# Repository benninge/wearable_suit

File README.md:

# Smart dancing suit

The smart dancing suit project was part of the [Wearable Computing Systems Lab Course](https://es.informatik.uni-freiburg.de/teaching/wearable-lab) during the summer semester of 2017. The idea is to develop an LED covered dancing suit which generates a light show according to the current music and movements of the wearer, instead of running a predefined choreography like it is done in other approaches. This is what makes the suit a “smart" dancing suit.

Therefore the suit is equipped with a couple of sensors, which enable sensing of motions and sound. For the sound measurement, a microphone module is used. The measurement samples are then used to calculate the sound level or to apply a Fourier transform. The music spectrum can be shown on the chest display.
The motion measurements are performed by inertial measurement units (IMUs) which are mounted on hands and feet. This allows movement detection of individual body parts.

## Contents

* [System architecture](https://github.com/benninge/wearable_suit/blob/master/README.md#hardware-architecture)
    * [Mainboard](https://github.com/benninge/wearable_suit/blob/master/README.md#mainboard)
    * [Sensor Board](https://github.com/benninge/wearable_suit/blob/master/README.md#sensor-board)
* [Software](https://github.com/benninge/wearable_suit/blob/master/README.md#software)
    * [Mainboard firmware](https://github.com/benninge/wearable_suit/blob/master/README.md#mainboard-firmware)
    * [Sensor board firmware](https://github.com/benninge/wearable_suit/blob/master/README.md#sensor-board-firmware)
    * [App](https://github.com/benninge/wearable_suit/blob/master/README.md#app)

## Hardware architecture

The system is built according to the hardware architecture given in figure 1. The centerpiece of the system is the mainboard. It contains an STM32 microcontroller, which controls all the other modules. It is connected to the IMU sensor modules over a bus systems and it directly controls all LEDs as well as the microphone module, which is used for music detection. A bluetooth connection to an Android app was also planned, but is currently not implemented.

<figure role="group">
<div align="center"></div> 
<div align="center"><figcaption> Figure 1: Schematic setup of the system </figcaption></div> 
</figure>

### Mainboard

The mainboard consists of an STM32F411E discovery board with a breadboard shield. The shield powers the discovery board and connects it to the sensor boards, the WS2812 RGB LED strips on arms and legs, the 10 x 10 LED display on the chest and the Adafruit MAX9814 microphone module. A wiring diagram of the mainboard shield is shown in figure 2.

<figure role="group">
<div align="center"></div> 
<div align="center"><figcaption> Figure 2: Wiring diagram of the mainboard shield </figcaption></div> 
</figure>

The sensor boards are connected over an RS-485 based bus system. The RS-485 transceiver should be a model with a 3.3V logic level. The chest display and the LED strips have to be connected according to the defines in the header files WS2812.h, ledSuit.h and the source file ledSuit.c of the mainboard firmware (which may be configured according to the used led-strip lengths). Since the LED strips are powered with 5V, each LED strip uses a switching regulator to generate its supply voltage out of the 3s LiPo power supply (which is called VCC here).

### Sensor board

The sensor module is an Arduino compatible custom circuit board. Figure 3 shows an assembled sensor board. The EAGLE files can be found in the "SensorBoard" folder in this repository. The sensor board hardware uses an ATmega328P microcontroller and a MPU-9250 IMU. It is directly powered by the 3s LiPo power supply and connected to the mainboard over the RS-485 bus.

<figure role="group">
<div align="center"></div> 
<div align="center"><figcaption> Figure 3: Sensor board </figcaption></div> 
</figure>

## Software

This project provides a software development kit for the mainboard containing examples. Additionally, a sensor board firmware is provided as well as an incomplete Android app to control the suit with a smartphone.

### Mainboard firmware

The mainboard firmware can be found in the "mainboard" folder. It contains all libraries for developing your own project as well as some example programs which show the capabilities of the provided libraries.

#### Libraries

The module structure of the mainboard firmware is shown in figure 4. The used hardware modules are colored in blue and the libraries are colored in green. The whole suit functionality can easily be accessed through high level functions, provided by the software development kit libraries. The example program libraries show how the software development kit can be used, to program specific applications.

<figure role="group">
<div align="center"></div> 
<div align="center"><figcaption> Figure 4: Module structure of the mainboard firmware </figcaption></div> 
</figure>

#### Examples

The smartSuit library offers some example programs which show the capabilities of the software development kit. The examples are directly called in the main function and can be chosen by passing a different demo number to the smartSuit_demo function :
```c
void smartSuit_demo(int demoNumber);
```
The following demos are available:

1. Music spectrum and color fade auto rotate demo: Shows the music spectrum on the chest display and an automatically rotating color fade on arms and legs.
2. Sound level and moving demo: Lights up moving body parts with an automatically rotating color fade. The suit brightness depends on the sound level.
3. Music spectrum and strobe moving demo: Shows the music spectrum on the chest display and lights up moving body parts with a strobe.
4. Moving and auto color fade demo: Fades the color of the whole Suit and lights up moving body parts.
5. Pulse and smiley demo: Shows moving pulses on arms and legs and a smiley on the chest display.
6. Play Simon says: An implementation of the game "Simon says". The suit displays body movements, which the wearer has to reproduce.

### Sensor board firmware

Before flashing the firmware to the sensor boards, the Arduino bootloader needs to be flashed to the sensor boards according to the [Arduino ISP instructions](https://www.arduino.cc/en/Tutorial/ArduinoISP). The sensor board firmware can be found in the "arduino/src/mpu9250_basicDMP" folder.

The Digital Motion Processor (DMP) on the IMU of each sensor board performs 6-axis sensor fusion (ignoring the integrated magnetometer and barometer) using the [motion driver library](http://www.digikey.de/en/pdf/i/invensense/motion-driver-6-1-user-guide) of Invensense. The resulting quaternions and acceleration values are transmitted over I^2C to the ATmega328P microcontroller 100 times per second. The microcontroller then converts the quaternions into the Euler coordinate system and normalizes the acceleration values into multiples of g = 9.81 m/s^2. 9-axis fusion is possible using the MPU9250, but would result in a slower update rate and additional need to calibrate the magnetometer each time the suit is powered up.

A master-slave communication over RS485 is used to communicate these values from each sensor board to the mainboard. The master (mainboard) requests new sensor values of one slave (sensor board) at a time. This avoids possible packet collisions on the bus. To differentiate the sensor boards from each other, the SLAVE_ID in mpu9250_basicDMP.ino has to be set to a value between 1 and 4 which represents the sensor boards specific ID. Once a sensor board receives a request for new values, it checks if the request was meant for its SLAVE_ID. If that is the case, it sends back a package with the current yaw, pitch, roll, the current rates at which these values change, and the 3-axis acceleration values.

The following values for SLAVE_ID are used:
* SLAVE_ID = 1: left arm
* SLAVE_ID = 2: right arm
* SLAVE_ID = 3: left leg
* SLAVE_ID = 4: right leg

### App

The "App" folder contains the app source code. The app is programmed with Android Studio and therefore available for Android devices. With the help of the "Dancing Suit" app, the user can select features for the suit. The app runs on a smartphone but cannot connect to the suit yet, because the Bluetooth communication to the mainboard is not fully implemented.

The app starts with a splash screen. From the main activity the user can connect the suit to the Bluetooth module and slide in a navigation drawer. It contains the navigation destinations "Right Arm", "Left Arm", "Right Leg", "Left Leg", "Suit", "Demo", "Info" and "Share". A screenshot of the navigation drawer is shown in figure 5 (left). The user can control each body part separately, set settings for the hole suit, get information about the developer and find the share link for github.

In the activity COLOR, which is shown in figure 5 (middle), the settings for colors can be set. The checkboxes allow the user to select the colors. Furthermore, there are activities for the COLORFADE function and the AUTOCOLORFADE function. To get an overview about the functions and what they do, check out the header file "ledSuit.h" in the mainboard firmware. For each of the three activities, there is a spinner to choose the blinking pattern of the suit. Figure 5 (right) shows the contents in a pop-up dialog.

<figure role="group">
<div align="center">

</div> 
<div align="center"><figcaption> Figure 5: Navigation drawer of the Dancing Suit app (left), activity for color settings (middle) and spinner dialog for blinking pattern (right)</figcaption></div> 
</figure>

To implement the wireless data exchange the Android Bluetooth APIs are used. Following the guide from 
[Android Developers](https://developer.android.com/guide/topics/connectivity/bluetooth.html), scanning for Bluetooth devices and adapting to the module with an insert mac address works but there is no function for data transmission.

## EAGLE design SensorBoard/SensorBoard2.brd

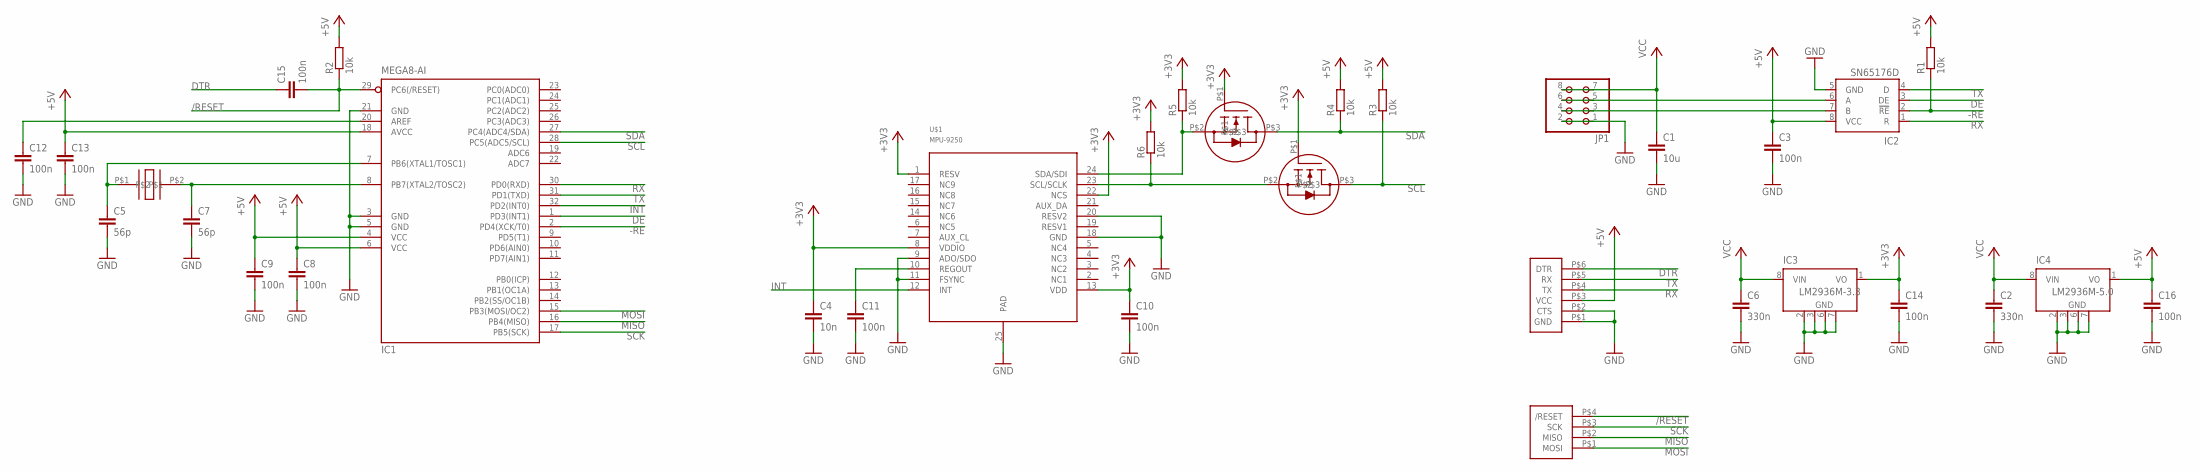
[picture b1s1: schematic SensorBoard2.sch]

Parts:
C1: 10u; C0805
C2, C6: 330n; C0603
C3, C8, C9, C10, C11, C12, C13, C14, C15, C16: 100n; C0603
C4: 10n; C0603
C5, C7: 56p; C0603
IC1: MEGA8-AI; TQFP32-08
IC2: SN65176D; SO-08
IC3: LM2936M-3.3; SO08
IC4: LM2936M-5.0; SO08
JP1: PINHD-2X4/90; 2X04/90
R1, R2, R3, R4, R5, R6: 10k; R0603
U$1: MPU-9250; LEAD-QFN24
U$2, U$3: 2N7002E; SOT-23-3
U$4: LFXTAL003240BULK
U$5: FTDI-PINHEADER
U$6: ISP_PADS

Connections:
+3V3: C4.1, C10.1, C14.1, IC3.1 (VO), R5.2, R6.2, U$1.1 (RESV), U$1.8 (VDDIO), U$1.13 (VDD), U$1.22 (NCS), U$2.P$1, U$3.P$1
+5V: C3.1, C8.1, C9.1, C13.1, C16.1, IC1.4 (VCC), IC1.6 (VCC), IC1.18 (AVCC), IC2.8 (VCC), IC4.1 (VO), R1.2, R2.2, R3.2, R4.2, U$5.P$3 (VCC)
-RE: IC1.2 (PD4(XCK/T0)), IC2.2 (!RE), R1.1
/RESET: C15.2, IC1.29 (PC6(/RESET)), R2.1, U$6.P$4 (/RESET)
DE: IC1.1 (PD3(INT1)), IC2.3 (DE)
DTR: C15.1, U$5.P$6 (DTR)
GND: C1.2, C2.2, C3.2, C4.2, C5.2, C6.2, C7.2, C8.2, C9.2, C10.2, C11.2, C12.2, C13.2, C14.2, C16.2, IC1.3 (GND), IC1.5 (GND), IC1.21 (GND), IC2.5 (GND), IC3.2 (GND), IC3.3 (GND), IC3.6 (GND), IC3.7 (GND), IC4.2 (GND), IC4.3 (GND), IC4.6 (GND), IC4.7 (GND), JP1.1, JP1.2, U$1.9 (ADO/SDO), U$1.11 (FSYNC), U$1.18 (GND), U$1.20 (RESV2), U$1.25 (PAD), U$5.P$1 (GND), U$5.P$2 (CTS)
INT: IC1.32 (PD2(INT0)), U$1.12 (INT)
MISO: IC1.16 (PB4(MISO)), U$6.P$2 (MISO)
MOSI: IC1.15 (PB3(MOSI/OC2)), U$6.P$1 (MOSI)
unnamed: IC2.6 (A), JP1.5, JP1.6
unnamed: IC2.7 (B), JP1.3, JP1.4
unnamed: R6.1, U$1.23 (SCL/SCLK), U$2.P$2
unnamed: C11.1, U$1.10 (REGOUT)
unnamed: C5.1, IC1.7 (PB6(XTAL1/TOSC1)), U$4.P$1
unnamed: R5.1, U$1.24 (SDA/SDI), U$3.P$2
unnamed: C7.1, IC1.8 (PB7(XTAL2/TOSC2)), U$4.P$2
unnamed: C12.1, IC1.20 (AREF)
RX: IC1.30 (PD0(RXD)), IC2.1 (R), U$5.P$4 (TX)
SCK: IC1.17 (PB5(SCK)), U$6.P$3 (SCK)
SCL: IC1.28 (PC5(ADC5/SCL)), R3.1, U$2.P$3
SDA: IC1.27 (PC4(ADC4/SDA)), R4.1, U$3.P$3
TX: IC1.31 (PD1(TXD)), IC2.4 (D), U$5.P$5 (RX)
VCC: C1.1, C2.1, C6.1, IC3.8 (VIN), IC4.8 (VIN), JP1.7, JP1.8

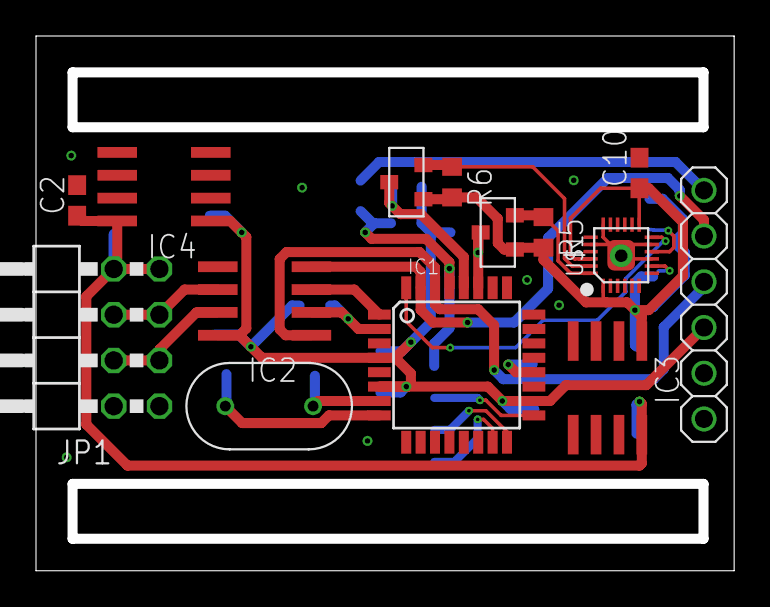
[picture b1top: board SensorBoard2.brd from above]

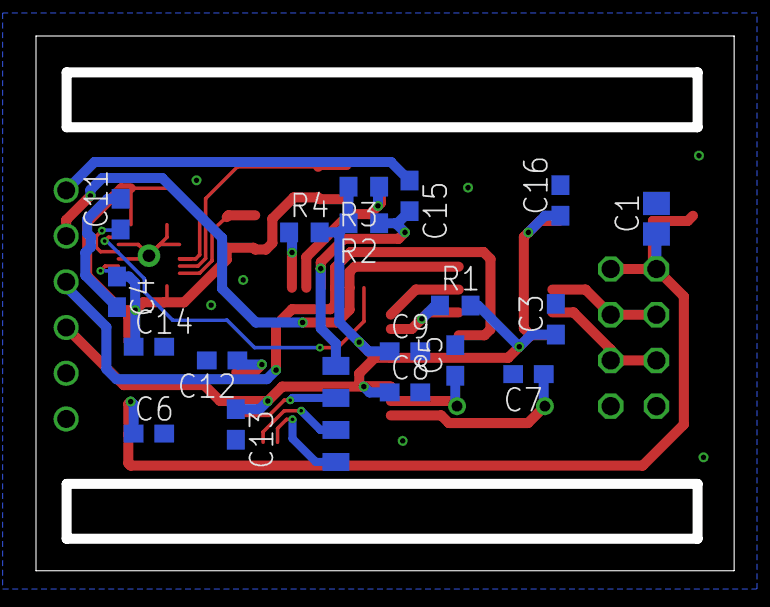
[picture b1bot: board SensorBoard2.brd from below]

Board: 2 copper layers, 38.2 x 29.1 mm, 33 parts (19 on the bottom side), 24 nets.

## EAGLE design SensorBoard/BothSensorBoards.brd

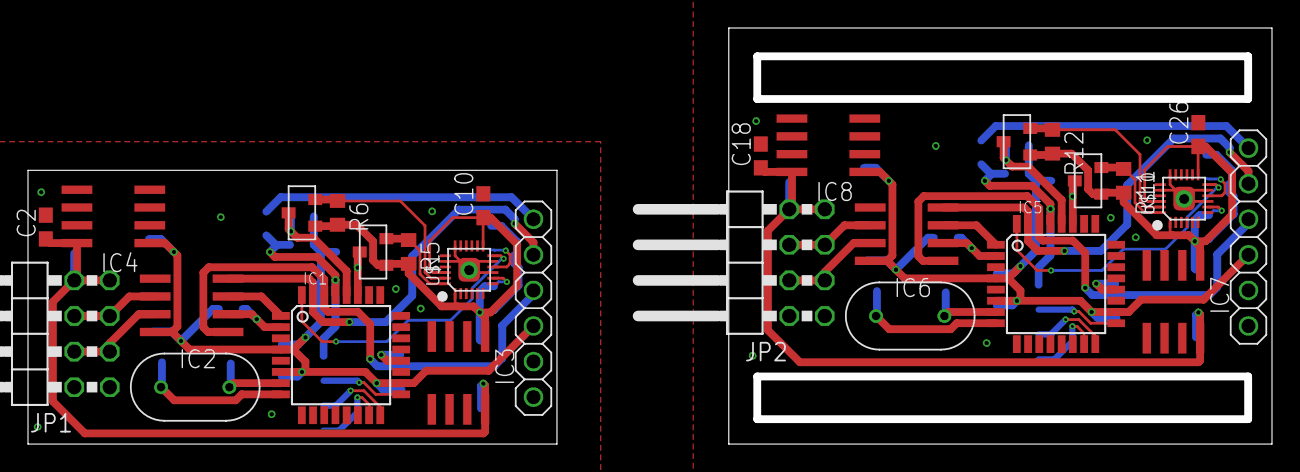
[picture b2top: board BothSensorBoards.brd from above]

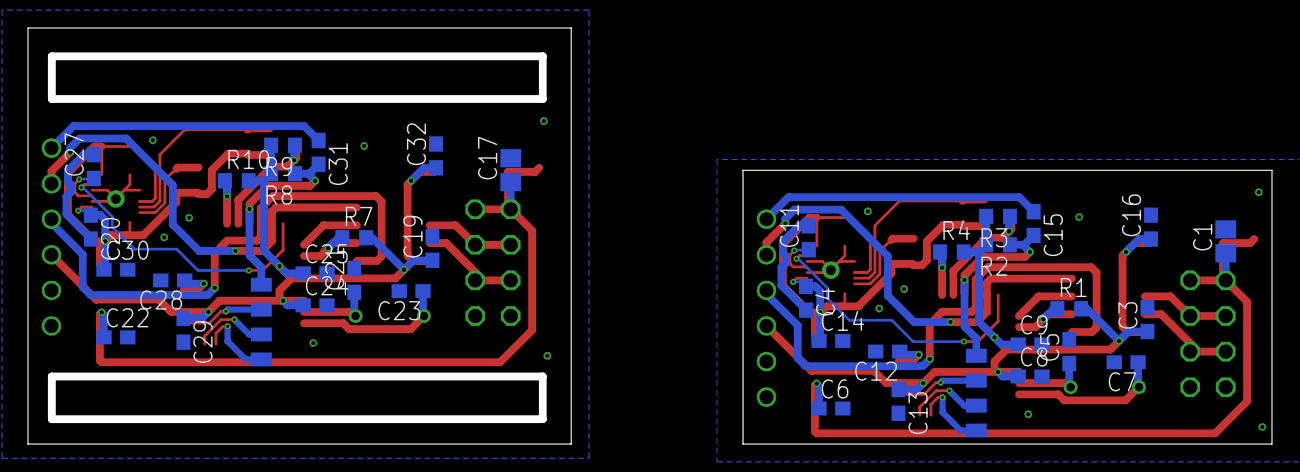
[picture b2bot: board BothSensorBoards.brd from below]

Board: 2 copper layers, 88.3 x 29.1 mm, 66 parts (38 on the bottom side), 48 nets.

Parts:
C1, C17: 10u; C0805
C2, C6, C18, C22: 330n; C0603
C3, C8, C9, C10, C11, C12, C13, C14, C15, C16, C19, C24, C25, C26, C27, C28, C29, C30, C31, C32: 100n; C0603
C4, C20: 10n; C0603
C5, C7, C21, C23: 56p; C0603
IC1, IC5: MEGA8-AI; TQFP32-08
IC2, IC6: SN65176D; SO-08
IC3, IC7: LM2936M-3.3; SO08
IC4, IC8: LM2936M-5.0; SO08
JP1, JP2: 2X04/90
R1, R2, R3, R4, R5, R6, R7, R8, R9, R10, R11, R12: 10k; R0603
U$1, U$10: MPU-9250; LEAD-QFN24
U$2, U$3, U$7, U$8: 2N7002E; SOT-23-3
U$4, U$9: LFXTAL003240BULK
U$5, U$11: FTDI-PINHEADER
U$6, U$12: ISP_PADS

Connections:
+3V1: C20.1, C26.1, C30.1, IC7.1, R11.2, R12.2, U$7.P$1, U$8.P$1, U$10.1, U$10.8, U$10.13, U$10.22
+3V3: C4.1, C10.1, C14.1, IC3.1, R5.2, R6.2, U$1.1, U$1.8, U$1.13, U$1.22, U$2.P$1, U$3.P$1
+5V: C3.1, C8.1, C9.1, C13.1, C16.1, IC1.4, IC1.6, IC1.18, IC2.8, IC4.1, R1.2, R2.2, R3.2, R4.2, U$5.P$3
+5V1: C19.1, C24.1, C25.1, C29.1, C32.1, IC5.4, IC5.6, IC5.18, IC6.8, IC8.1, R7.2, R8.2, R9.2, R10.2, U$11.P$3
-RE: IC1.2, IC2.2, R1.1
-RE1: IC5.2, IC6.2, R7.1
/RESET: C15.2, IC1.29, R2.1, U$6.P$4
/RESET1: C31.2, IC5.29, R8.1, U$12.P$4
DE: IC1.1, IC2.3
DE1: IC5.1, IC6.3
DTR: C15.1, U$5.P$6
DTR1: C31.1, U$11.P$6
GND: C1.2, C2.2, C3.2, C4.2, C5.2, C6.2, C7.2, C8.2, C9.2, C10.2, C11.2, C12.2, C13.2, C14.2, C16.2, IC1.3, IC1.5, IC1.21, IC2.5, IC3.2, IC3.3, IC3.6, IC3.7, IC4.2, IC4.3, IC4.6, IC4.7, JP1.1, JP1.2, U$1.9, U$1.11, U$1.18, U$1.20, U$1.25, U$5.P$1, U$5.P$2
GND1: C17.2, C18.2, C19.2, C20.2, C21.2, C22.2, C23.2, C24.2, C25.2, C26.2, C27.2, C28.2, C29.2, C30.2, C32.2, IC5.3, IC5.5, IC5.21, IC6.5, IC7.2, IC7.3, IC7.6, IC7.7, IC8.2, IC8.3, IC8.6, IC8.7, JP2.1, JP2.2, U$10.9, U$10.11, U$10.18, U$10.20, U$10.25, U$11.P$1, U$11.P$2
INT: IC1.32, U$1.12
INT1: IC5.32, U$10.12
MISO: IC1.16, U$6.P$2
MISO1: IC5.16, U$12.P$2
MOSI: IC1.15, U$6.P$1
MOSI1: IC5.15, U$12.P$1
unnamed: IC2.6, JP1.5, JP1.6
unnamed: IC2.7, JP1.3, JP1.4
unnamed: R6.1, U$1.23, U$2.P$2
unnamed: C11.1, U$1.10
unnamed: C5.1, IC1.7, U$4.P$1
unnamed: R5.1, U$1.24, U$3.P$2
unnamed: C7.1, IC1.8, U$4.P$2
unnamed: R12.1, U$7.P$2, U$10.23
unnamed: C12.1, IC1.20
unnamed: R11.1, U$8.P$2, U$10.24
unnamed: C27.1, U$10.10
unnamed: C21.1, IC5.7, U$9.P$1
unnamed: C23.1, IC5.8, U$9.P$2
unnamed: C28.1, IC5.20
unnamed: IC6.6, JP2.5, JP2.6
unnamed: IC6.7, JP2.3, JP2.4
RX: IC1.30, IC2.1, U$5.P$4
RX1: IC5.30, IC6.1, U$11.P$4
SCK: IC1.17, U$6.P$3
SCK1: IC5.17, U$12.P$3
SCL: IC1.28, R3.1, U$2.P$3
SCL1: IC5.28, R9.1, U$7.P$3
SDA: IC1.27, R4.1, U$3.P$3
SDA1: IC5.27, R10.1, U$8.P$3
TX: IC1.31, IC2.4, U$5.P$5
TX1: IC5.31, IC6.4, U$11.P$5
VCC: C1.1, C2.1, C6.1, IC3.8, IC4.8, JP1.7, JP1.8
VCC1: C17.1, C18.1, C22.1, IC7.8, IC8.8, JP2.7, JP2.8

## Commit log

2017-05-11 this is a test
2017-05-11 added empty hardware list
2017-05-11 updated hardware list
2017-05-14 added list of material
2017-05-14 updated list of material
2017-05-14 added list of material and sensor board schematic
2017-05-20 initial rs485 test files
2017-05-20 change to serial1 for arduino leonardo
2017-05-20 rs485 demo works
2017-05-21 changed delay to Serial.flush(), works
2017-05-21 added .gitignore
2017-05-21 fix master
2017-05-30 added eagle files for sensor board
2017-05-30 finished sensor board schematic
2017-05-30 finished sensor board layout
2017-05-31 made some non-functional changes on sensor board layout and schematic
2017-05-31 9DOF AHRS fusion, 21kb flash needed
2017-06-01 added basic DMP version, 17kb, seems to work
2017-06-02 added pads for flashing the bootloader to sensor board, added alternative version of sensor board
2017-06-15 added accel values, bugfixes
2017-06-15 initial dmp + rs485 commit, untested
2017-06-16 added missing library
2017-06-16 working prototype, pitch and roll flipped?
2017-06-18 added empty mainboard firmware project
2017-06-19 Added libraries for led strips and led suit to mainboard firmware
2017-06-21 fix project
2017-06-22 changed include
2017-06-22 replaced ws2811 library by own ws2812 library
2017-06-22 added 4 channel support to ws2812 library, refactored ledSuit library
2017-06-22 added 4 channel support to ws2812 library, refactored ledSuit library (reverted from commit 1cc2ef613847d8b94c4e8f30ec4543500a34e13e)
2017-06-22 added 4 channel support to ws2812 library, refactored ledSuit library (reverted from commit 1cc2ef613847d8b94c4e8f30ec4543500a34e13e) (reverted from commit d02fd2d8e26421906d317fddd71ffd60a5ddc54a)
2017-06-22 added 4 channel support to ws2812 library, refactored ledSuit library (reverted from commit 1cc2ef613847d8b94c4e8f30ec4543500a34e13e) (reverted from commit d02fd2d8e26421906d317fddd71ffd60a5ddc54a) (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
2017-06-23 Added a setBrightness function to ledSuit, did a bit of refactoring
2017-06-23 Added brightness and strobe functions to ledSuit library
2017-06-23 fixed bug in ws2812 library (bits were sent in wrong order)
2017-06-23 Added color fade, rotate and auto rotate functions to ledSuit library
2017-06-23 incomplete rs485 commit
2017-06-23 added stm32f4 data sheet and reference manual
2017-06-23 added interrupt code, not complete
2017-06-24 fixes
2017-06-24 added functions for coloring individual leds, added shift functions, added auto color fade functions
2017-06-24 even more fixes!
2017-06-25 modified arduino code for test purposes, USART interrupt does not work
2017-06-25 changed usart2 to 1
2017-06-25 replaced startup file
2017-06-25 usart receives something, but its garbled
2017-06-27 refactored ledSuit library
2017-06-27 Added demo program for mid term presentation
2017-06-27 ledSuit library is now using timer 2 instead of system tick timer
2017-06-27 // Made some readability changes in ledSuit.h, Moved defines from ledSuit.c to ledSuit.h
2017-06-28 bugfixes, almost works
2017-06-29 Demo Video App
2017-06-29 refactor rs485
2017-06-29 moved some defines from ledSuit.h to ledSuit.c
2017-06-30 minimal working rs485, ledsuit disabled
2017-07-02 reverted sensorboard code, added stm32 master slave requests for rs485, some occasional bad bits received?
2017-07-05 started working on microphone library, added CMSIS DSP libraries
2017-07-05 made some whitespace changes in ws2812 library
2017-07-06 added empty bluetooth library
2017-07-06 Implemented basic microphone library functionality
2017-07-06 added some comments to microphone library header
2017-07-13 added basic chest display support to ledSuit library
2017-07-13 did some FFT fine tuning, added sensitivity parameter to mic_getSpectrum function
2017-07-13 added function to display a spectrum on the chest display
2017-07-20 configured led suit and ws2812 libraries according to final hardware
2017-07-20 added some example main code
2017-07-23 increased baud of sensor module
2017-07-23 added incomplete poster
2017-07-24 changed enable pins
2017-07-25 modified led suits according to hardware changes
2017-07-25 added background image to poster
2017-07-25 modiefied poster background image brightness
2017-07-26 changed sensorboard firmware to send actual imu values, switched mainboard usart from delay to timer interrupt triggered
2017-07-26 added USART library for bluetooth USART
2017-07-26 made some further changes according to hardware changes in led suit and ws2812 lib
2017-07-26 fixed a bug in usart library
2017-07-26 change to interrupt based sending over usart
2017-07-26 remove delay by waiting on IT_TC before disabling DE
2017-07-28 added a bit of sensor board info to poster
2017-07-28 fix poster
2017-07-28 fix poster again
2017-07-28 fix again²
2017-07-28 modified poster
2017-07-28 more poster modifications
2017-07-28 Update Poster with the App Infos
2017-07-28 manually merged poster changes
2017-07-28 added support to request and receive from up to 4 sensor boards
2017-07-29 added functions to detect movement
2017-07-29 added getAudioLevel function to mainboard microphone library
2017-07-29 improved getMoving function
2017-07-29 improved getMoving method
2017-07-29 moved update of sensor values from main to rx/tx interrupt
2017-07-29 removed stupid ; in main
2017-07-29 changed poster background image
2017-07-29 Added suit picture with transparent background for app
2017-07-30 modified poster again
2017-07-30 added schematic files for last commit (modified poster again)
2017-07-30 change app background to our picture
2017-07-30 changed pictures and corrected spelling mistake
2017-07-30 made some minor changes on the poster
2017-07-30 added poster pdf
2017-08-01 corrected some typos
2017-08-01 added demo programs for final presentation
2017-08-02 added names to poster
2017-08-04 added app
2017-08-08 started working on readme
2017-08-08 trying to fix image link in readme (testcommit)
2017-08-08 trying to resize image in readme (testcommit)
2017-08-08 Readme WIP
2017-08-08 readme WIP, added table of contents
2017-08-09 reademe WIP added shield schematic
2017-08-09 readme WIP corrected typo
2017-08-09 fix some typos
2017-08-09 added decription for sensor board firmware
2017-08-09 added slave_id values
2017-08-09 readme WIP added mainboard firmware module structure image
2017-08-09 readme WIP mainboard firmware
2017-08-09 fixed typos in readme
2017-08-09 changing everything to passive voice in readme
2017-08-09 fixed typo in readme
2017-08-10 fixed some typos in readme
2017-08-10 made minor change in readme
2017-08-10 update read me with text for app
2017-08-10 for readme file app image
2017-08-10 update readme with picture for app
2017-08-10 update with hyperlink
2017-08-11 fixed some spelling errors in readme
2017-08-11 readme test commit
2017-08-11 rearranged the app images in the readme file
2017-08-11 changed image position in readme
